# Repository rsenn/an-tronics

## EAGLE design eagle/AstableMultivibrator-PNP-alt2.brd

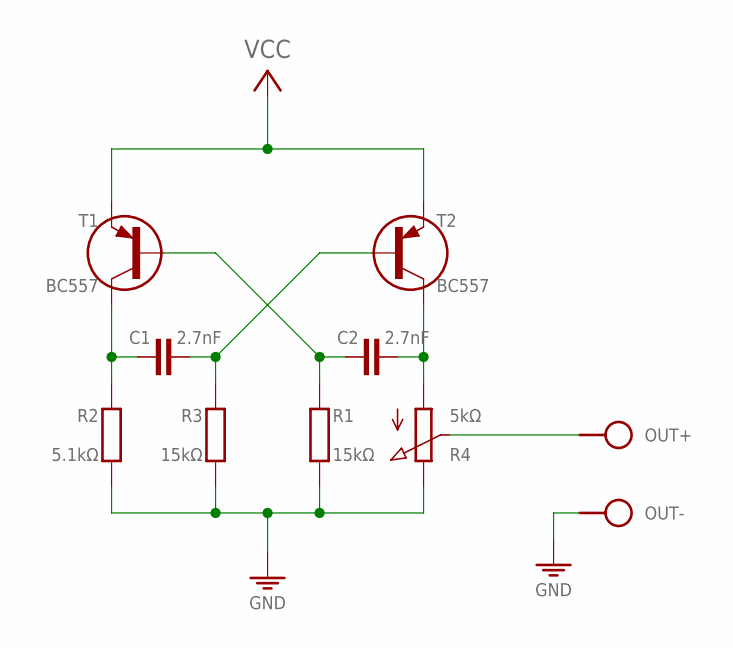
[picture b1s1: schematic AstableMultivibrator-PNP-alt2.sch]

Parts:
C1, C2: 2.7nF; C075-020X044
J1: VCC_GNDPWR-L; PWR-L
OUT: SPAD+--+; SPAD-+
R1, R3: 15kΩ; 0202/7-V
R2: 5.1kΩ; 0202/7-V
R4: 5kΩ; POT-V
T1, T2: BC557; TO92-CBE

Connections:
GND: J1.1 (GND), OUT.1, R1.1 (2), R2.1 (2), R3.1 (2), R4.E
unnamed: C2.2, R4.A, T2.C
unnamed: C1.1, R2.2 (1), T1.C
unnamed: C2.1, R1.2 (1), T1.B
unnamed: C1.2, R3.2 (1), T2.B
unnamed: OUT.2, R4.S
VCC: J1.2 (VCC), T1.E, T2.E

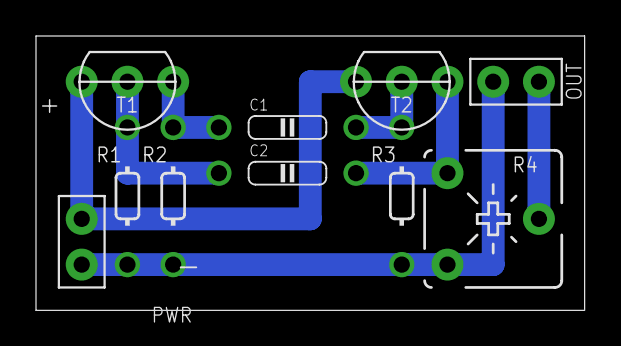
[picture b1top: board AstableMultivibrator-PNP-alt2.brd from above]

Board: 2 copper layers, 30.5 x 15.2 mm, 10 parts (0 on the bottom side), 7 nets.

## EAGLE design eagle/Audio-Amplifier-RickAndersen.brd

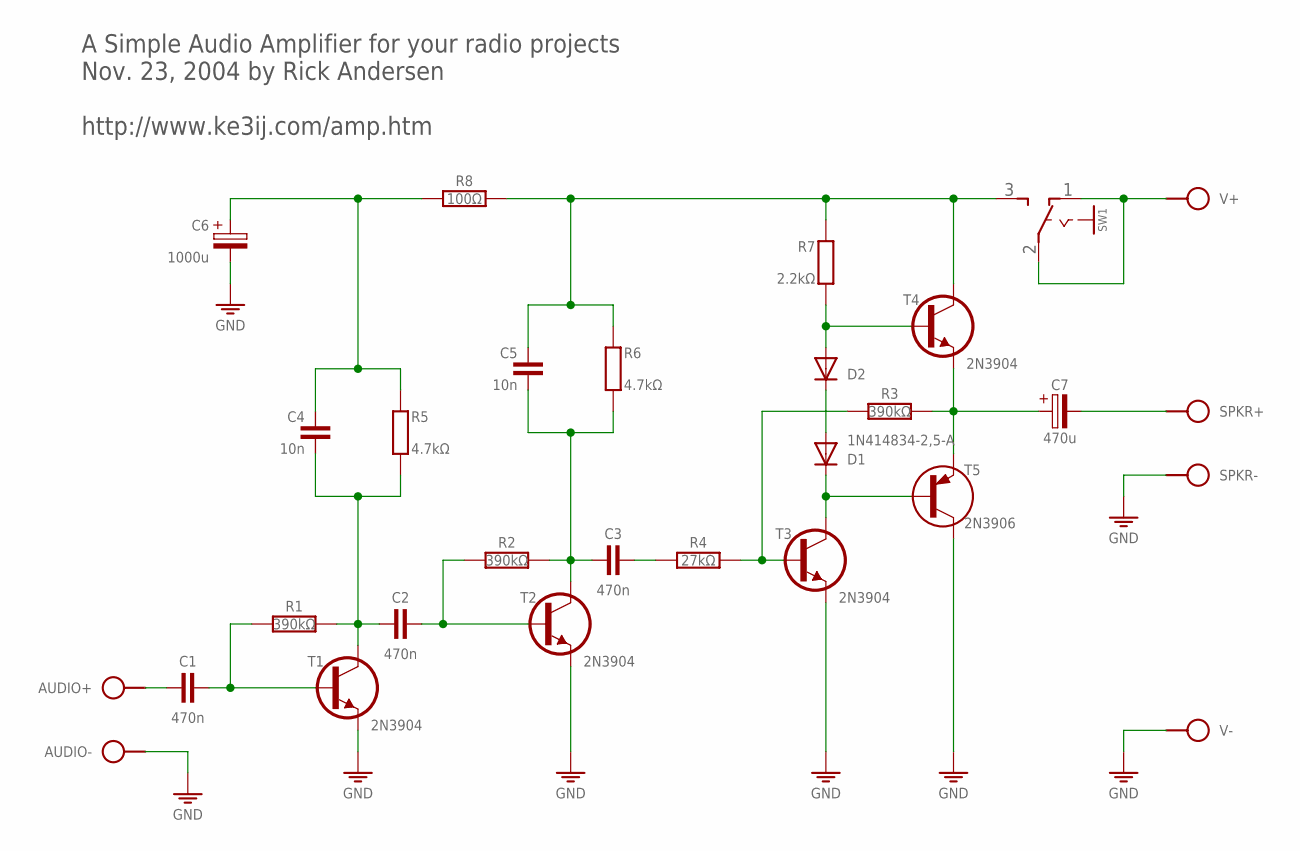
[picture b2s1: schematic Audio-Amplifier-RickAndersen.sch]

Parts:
AUDIO: SPAD+-+-; SPAD+-
C1, C2, C3: 470n; C050-020X044
C4, C5: 10n; C025-015X024
C6: 1000u; E5-6
C7: 470u; E5-6
D1: 1N414834-2,5-A; DO34-2,5-A
D2: 1N414834-5V; DO34-5V
R1, R2, R3: 390kΩ; 0202/7-V
R4: 27kΩ; 0202/7-V
R5, R6: 4.7kΩ; 0202/7-V
R7: 2.2kΩ; 0202/7
R8: 100Ω; 0202/7
SPKR: SPAD+-+-; SPAD+-
SW1: SL-SW-1P-2T-H; SLSW-1P2T-H
T1, T2, T3, T4: 2N3904; TO92
T5: 2N3906; TO92
V+: SPAD
V-: SPAD

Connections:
GND: AUDIO.1, C6.-, SPKR.1, T1.1 (E), T2.1 (E), T3.1 (E), T5.3 (C), V-.1
unnamed: C1.2, R1.1, T1.2 (B)
unnamed: C7.+, R3.2, T4.1 (E), T5.1 (E)
unnamed: C2.2, R2.1, T2.2 (B)
unnamed: D1.C, T3.3 (C), T5.2 (B)
unnamed: R3.1, R4.2, T3.2 (B)
unnamed: C3.2, R4.1
unnamed: C2.1, C4.2, R1.2, R5.2, T1.3 (C)
unnamed: C4.1, C6.+, R5.1, R8.1
unnamed: C3.1, C5.2, R2.2, R6.2, T2.3 (C)
unnamed: SW1.1 (O), SW1.2, V+.1
unnamed: D1.A, D2.C
unnamed: D2.A, R7.2, T4.2 (B)
unnamed: C5.1, R6.1, R7.1, R8.2, SW1.3 (S), T4.3 (C)
unnamed: AUDIO.2, C1.1
unnamed: C7.-, SPKR.2

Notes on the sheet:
A Simple Audio Amplifier for your radio projects Nov. 23, 2004 by Rick Andersen http://www.ke3ij.com/amp.htm

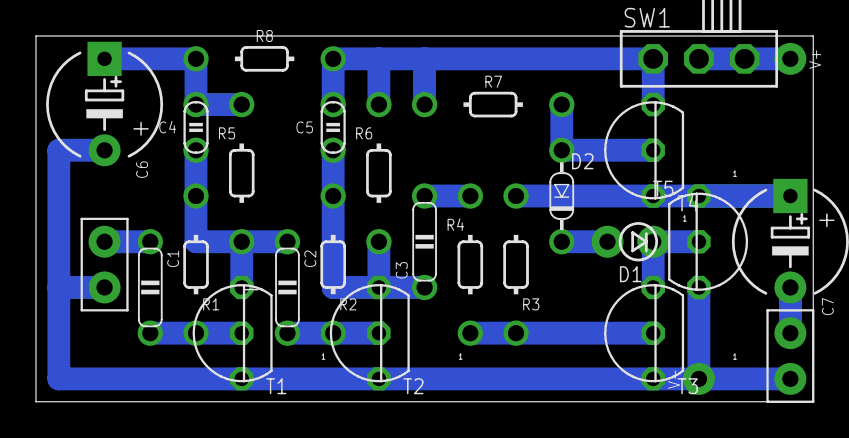
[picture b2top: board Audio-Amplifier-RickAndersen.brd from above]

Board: 2 copper layers, 43.2 x 20.3 mm, 27 parts (0 on the bottom side), 16 nets.

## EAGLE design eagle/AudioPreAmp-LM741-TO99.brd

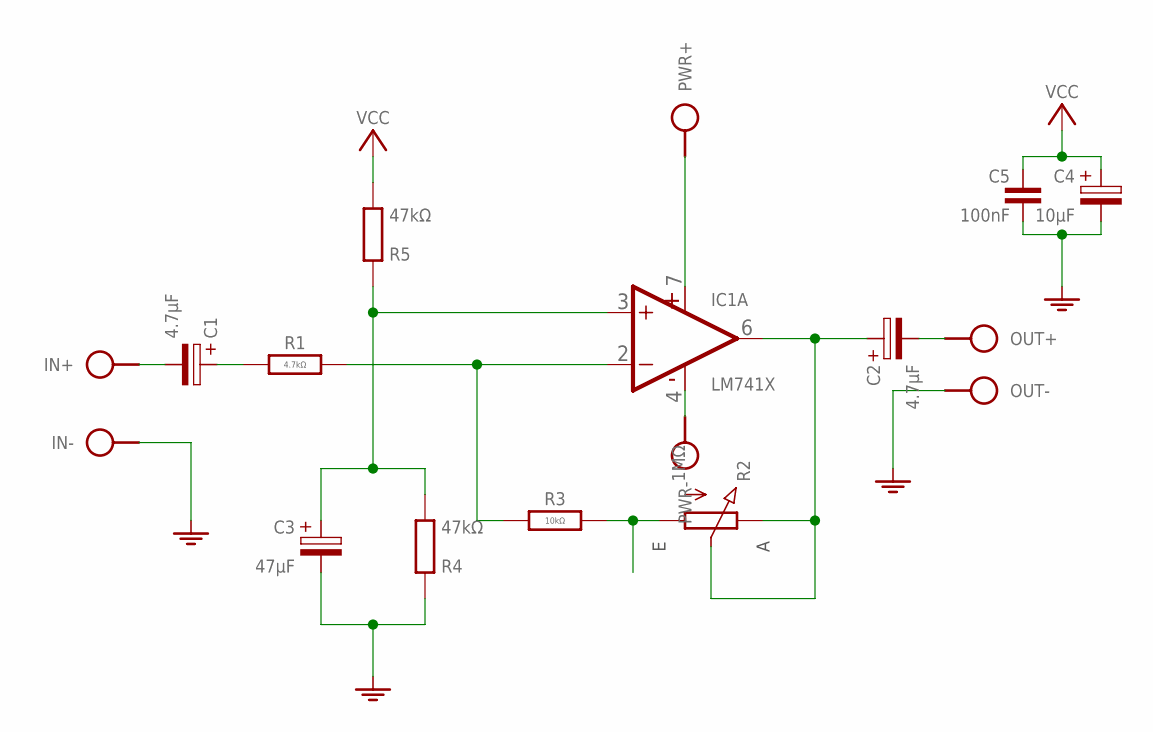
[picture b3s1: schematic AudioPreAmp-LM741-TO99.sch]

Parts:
C1: 4.7μF; E2.5-4/V
C2: 4.7μF; E5-4
C3: 47μF; E2,5-4
C4: 10μF; E2,5-3
C5: 100nF; C050-020X044/V
IC1: LM741X; TO99-X
IN: SPAD+--+; SPAD-+
OUT: SPAD+-+-; SPAD+-
PWR+: HPORT; SPAD
PWR-: HPORT; SPAD
R1: 4.7kΩ; 0204/10
R2: 1MΩ; CONN-3P
R3: 10kΩ; 0204/10-V
R4: 47kΩ; 0204/10-V
R5: 47kΩ; 0204/10

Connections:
AF: C2.-, OUT.2
GND: C3.-, C4.-, C5.2, IN.1, OUT.1, R4.1 (2)
IN+: C3.+, IC1.3 (+IN), R4.2 (1), R5.1 (2)
IN-: IC1.2 (-IN), R1.2, R3.1
unnamed: R2.1 (A), R3.2
unnamed: C1.+, R1.1
unnamed: IC1.4 (V-), PWR-.1
unnamed: C1.-, IN.2
unnamed: C2.+, IC1.6 (OUT), R2.2 (S), R2.3 (E)
PWR+: IC1.7 (V+), PWR+.1
VCC: C4.+, C5.1, R5.2 (1)

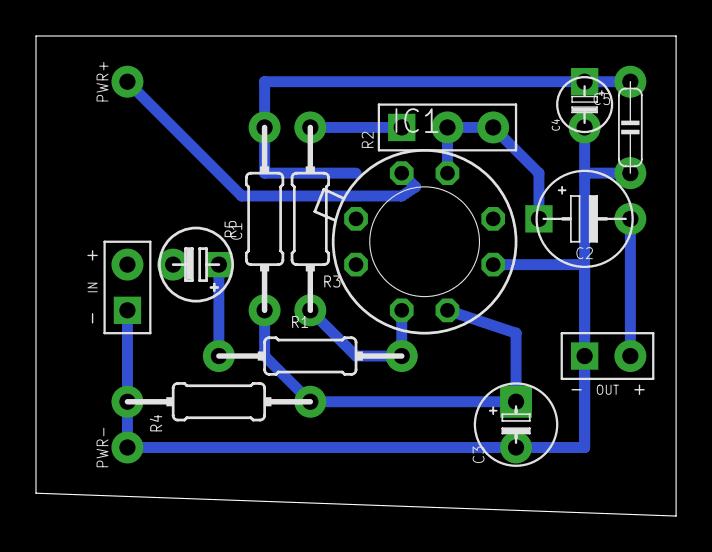
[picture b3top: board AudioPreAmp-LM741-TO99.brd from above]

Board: 2 copper layers, 35.6 x 26.7 mm, 15 parts (0 on the bottom side), 11 nets.

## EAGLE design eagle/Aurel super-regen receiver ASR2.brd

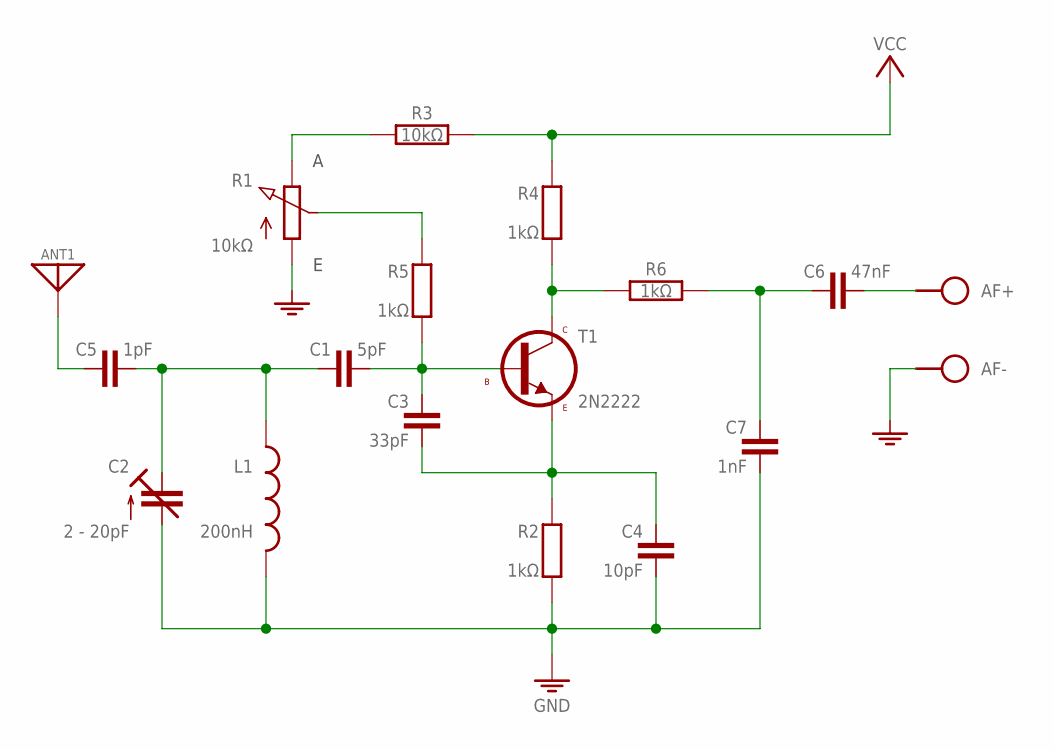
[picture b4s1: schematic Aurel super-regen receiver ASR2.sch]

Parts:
AF: SPAD+-+-; SPAD+-
ANT1: ANT; SPAD
C1: 5pF; C025-015X024
C2: 2 - 20pF; TRIM-2222-808
C3: 33pF; C025-015X024
C4: 10pF; C025-015X024
C5: 1pF; C025-015X024
C6: 47nF; C050-020X044
C7: 1nF; C050-020X044/V
L1: 200nH; L-04/7-V
R1: 10kΩ; POT
R2, R4, R5: 1kΩ; 0204/10-V
R3: 10kΩ; 0204/10
R6: 1kΩ; 0204/10
S2: VCC_GNDPWR-L; PWR-L
T1: 2N2222; TO92-EBC

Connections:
GND: AF.1, C2.2 (A), C4.2, C7.2, L1.2, R1.A, R2.2 (1), S2.1 (GND)
unnamed: ANT1.1, C5.1
unnamed: C1.1, C2.3 (E), C5.2, L1.1
unnamed: C1.2, C3.1, R5.2 (1), T1.B
unnamed: C3.2, C4.1, R2.1 (2), T1.E
unnamed: R4.2 (1), R6.1, T1.C
unnamed: R1.S, R5.1 (2)
unnamed: R1.E, R3.1
unnamed: C6.1, C7.1, R6.2
unnamed: AF.2, C6.2
VCC: R3.2, R4.1 (2), S2.2 (VCC)

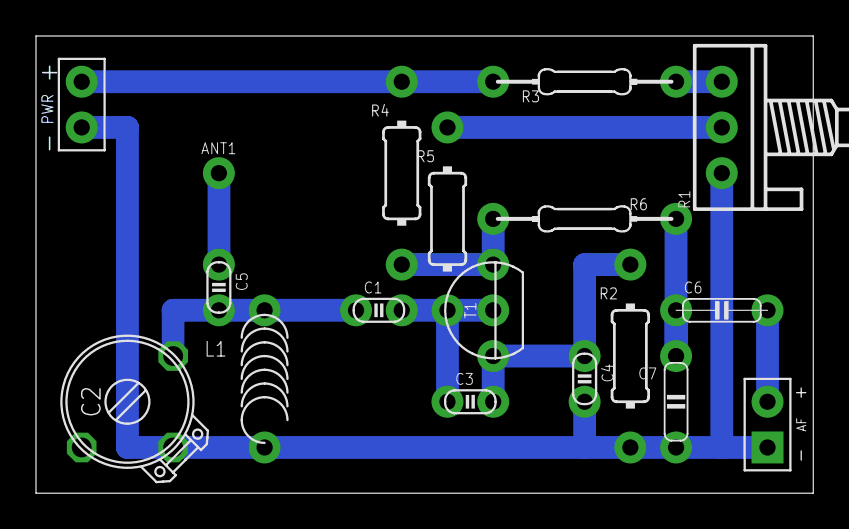
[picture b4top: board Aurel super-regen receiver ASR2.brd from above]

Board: 2 copper layers, 43.2 x 25.4 mm, 18 parts (0 on the bottom side), 11 nets.

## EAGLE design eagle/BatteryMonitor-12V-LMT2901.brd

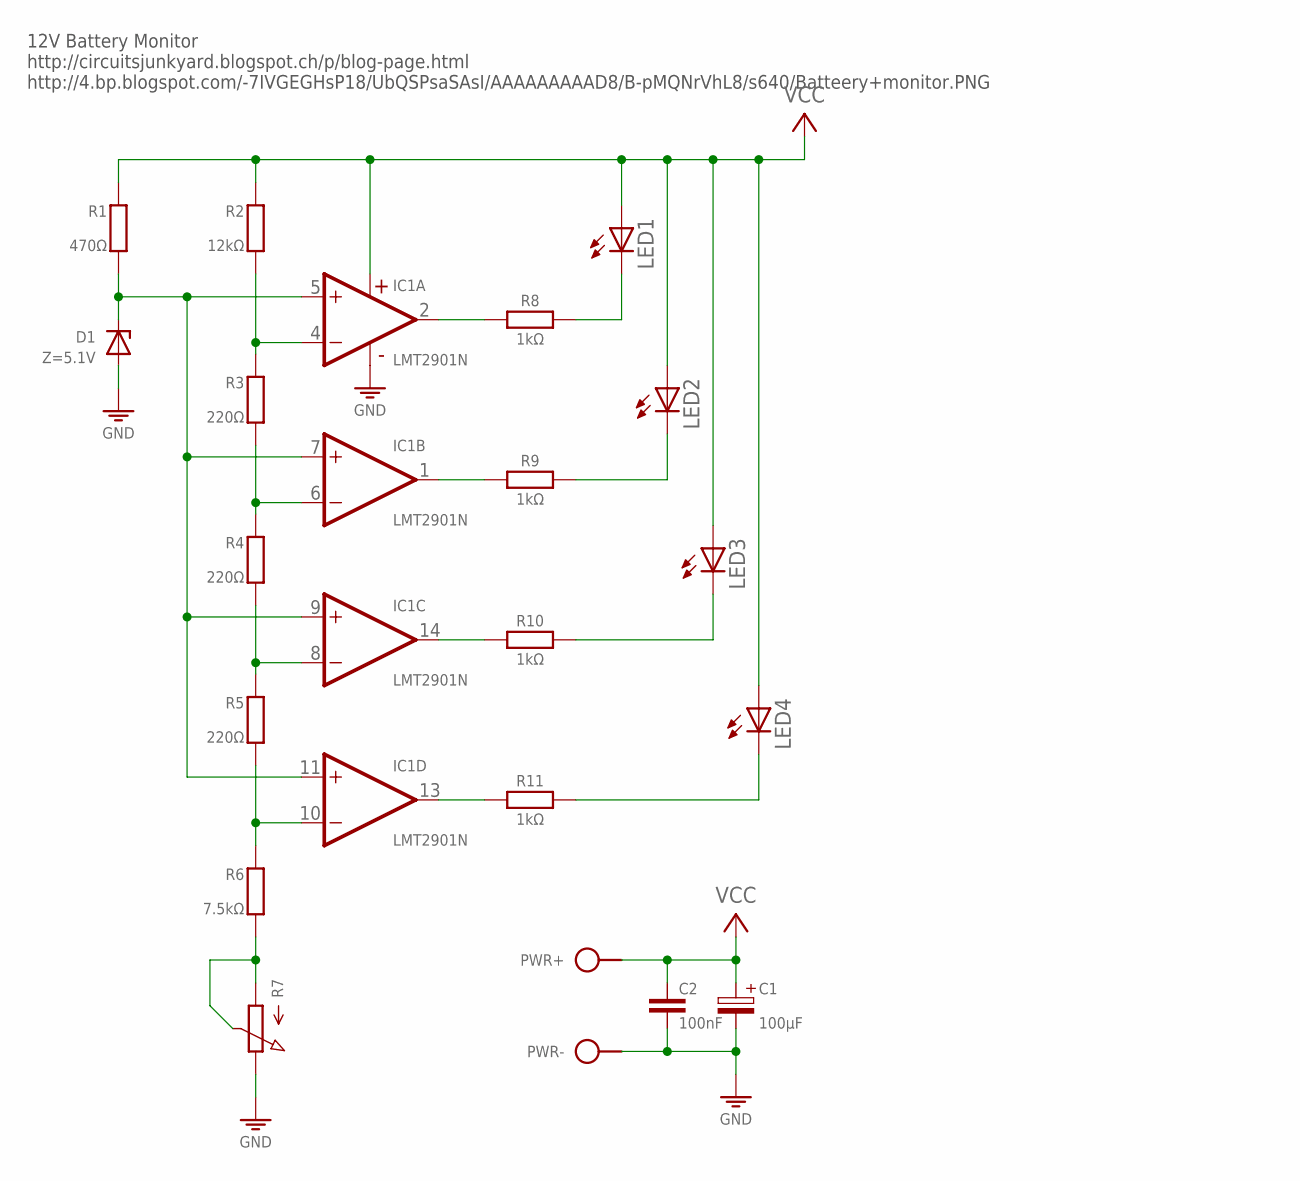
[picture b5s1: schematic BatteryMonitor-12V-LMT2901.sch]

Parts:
C1: 100μF; E2,5-4
C2: 100nF; C050-020X044
D1: Z=5.1V; DO34Z5V
IC1: LMT2901N; DIL14
LED1, LED2, LED3, LED4: LED3MM
PWR: SPAD+-
R1: 470Ω; 0204/10
R2: 12kΩ; 0204/10
R3, R4, R5: 220Ω; 0204/10
R6: 7.5kΩ; 0204/10
R7: POT
R8, R9, R10, R11: 1kΩ; 0204/10

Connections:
GND: C1.-, C2.2, D1.A, IC1.12 (V-), PWR.1, R7.3 (E)
unnamed: LED4.K (C), R11.2
unnamed: LED3.K (C), R10.2
unnamed: LED2.K (C), R9.2
unnamed: LED1.K (C), R8.2
unnamed: IC1.2 (OUT), R8.1
unnamed: IC1.1 (OUT), R9.1
unnamed: IC1.14 (OUT), R10.1
unnamed: IC1.13 (OUT), R11.1
unnamed: D1.C, IC1.5 (+IN), IC1.7 (+IN), IC1.9 (+IN), IC1.11 (+IN), R1.1
unnamed: IC1.4 (-IN), R2.1, R3.2
unnamed: IC1.6 (-IN), R3.1, R4.2
unnamed: IC1.8 (-IN), R4.1, R5.2
unnamed: IC1.10 (-IN), R5.1, R6.2
unnamed: R6.1, R7.1 (A), R7.2 (S)
VCC: C1.+, C2.1, IC1.3 (V+), LED1.A, LED2.A, LED3.A, LED4.A, PWR.2, R1.2, R2.2

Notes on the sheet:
12V Battery Monitor http://circuitsjunkyard.blogspot.ch/p/blog-page.html http://4.bp.blogspot.com/-7IVGEGHsP18/UbQSPsaSAsI/AAAAAAAAAD8/B-pMQNrVhL8/s640/Batteery+monitor.PNG

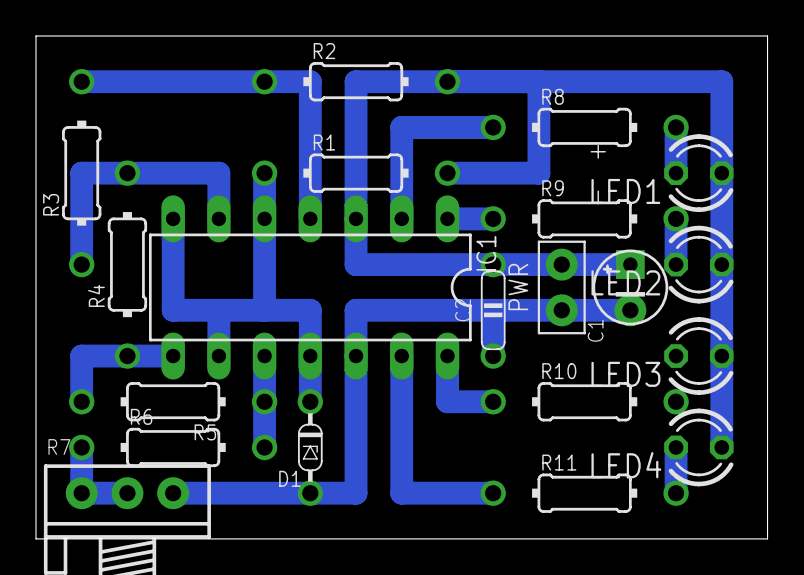
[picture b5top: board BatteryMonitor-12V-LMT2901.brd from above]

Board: 2 copper layers, 40.6 x 27.9 mm, 20 parts (0 on the bottom side), 16 nets.
